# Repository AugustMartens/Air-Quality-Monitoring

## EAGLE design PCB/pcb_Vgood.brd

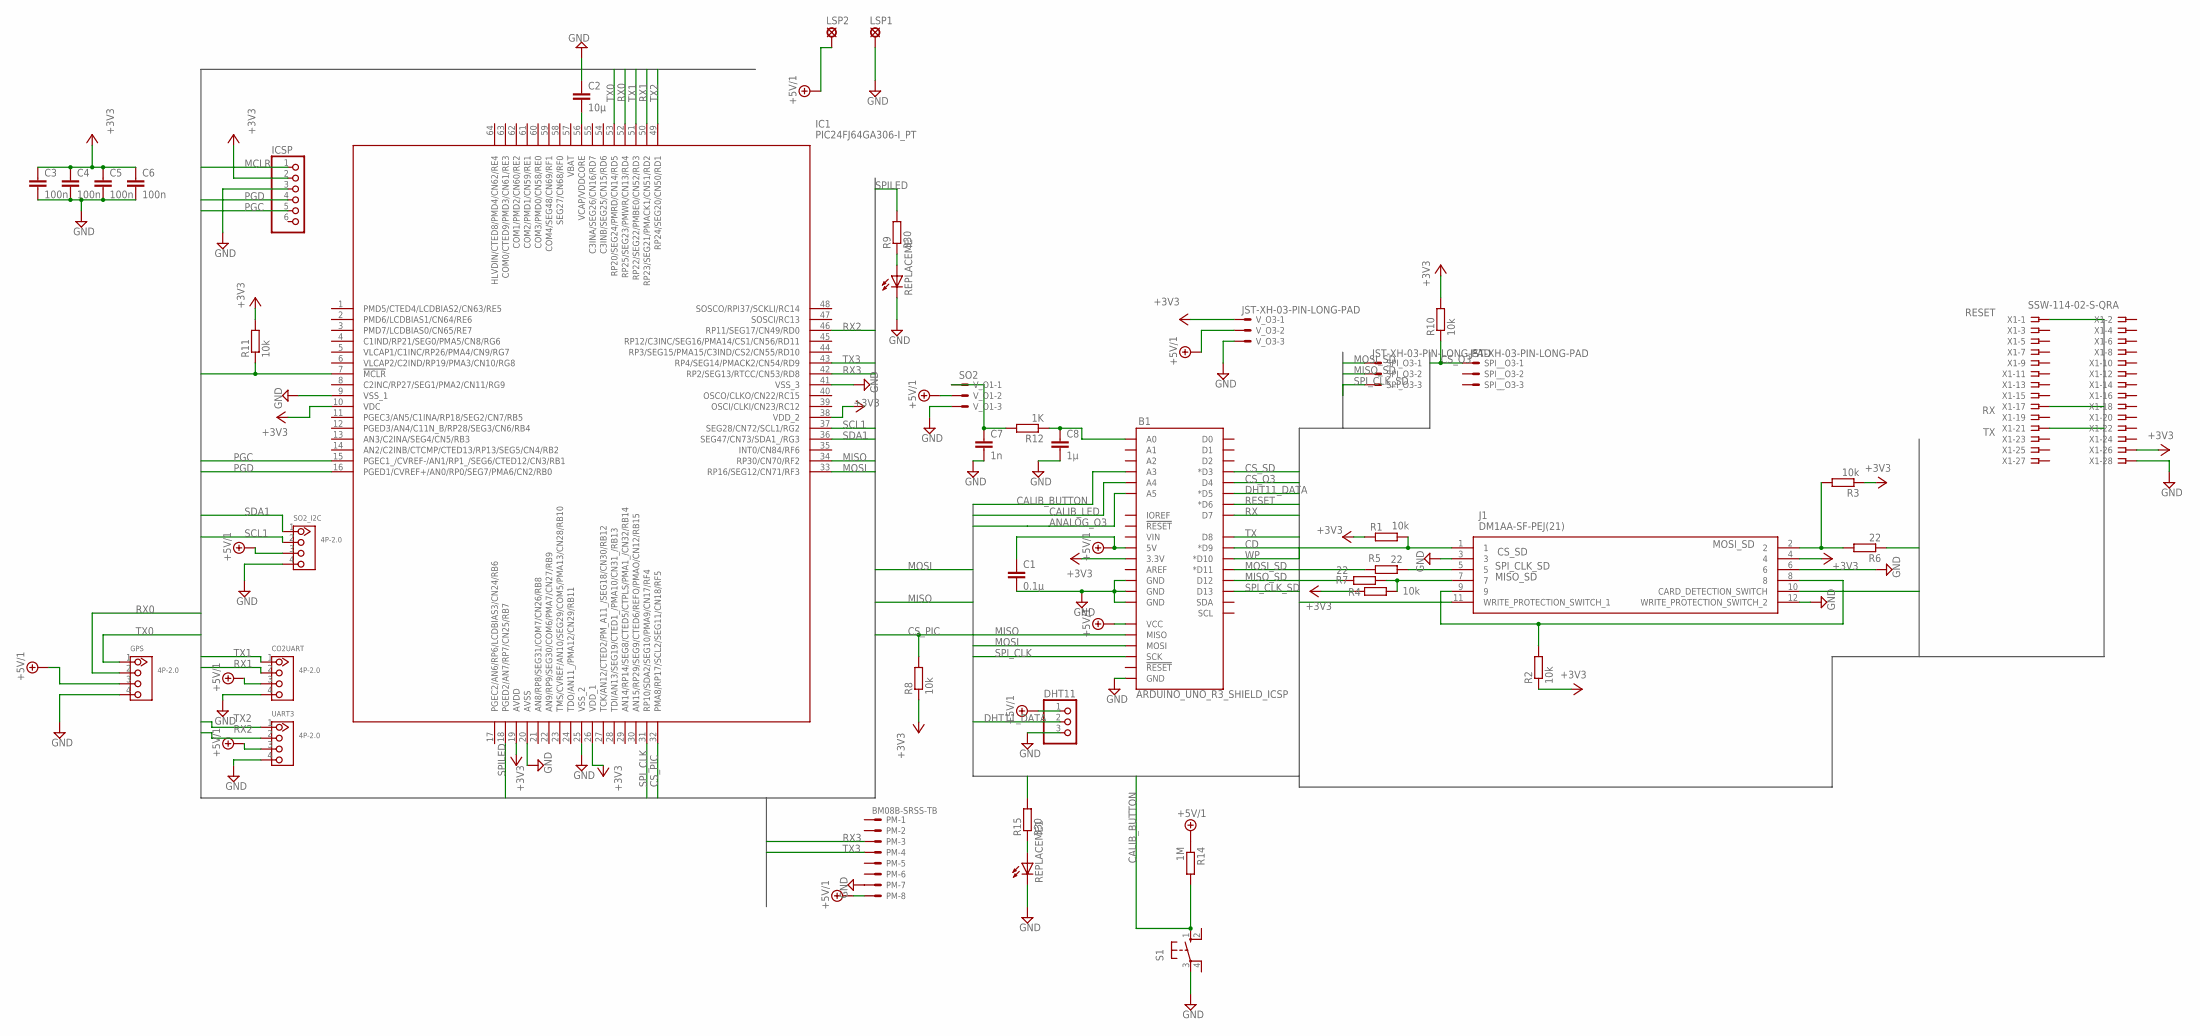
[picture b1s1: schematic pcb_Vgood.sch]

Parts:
B1: ARDUINO_UNO_R3_SHIELD_ICSP; UNO_R3_SHIELD_ICSP
C1: 0.1µ; C0805
C2: 10µ; C0805
C3, C4, C5, C6: 100n; C0805
C7: 1n; C0805
C8: 1µ; C0805
CO2UART: 4P-2.0; HW4-2.0
DHT11: PINHD-1X3; 1X03
GPS: 4P-2.0; HW4-2.0
IC1: PIC24FJ64GA306-I_PT; QFP50P1200X1200X120-64N
ICSP: PINHD-1X6; 1X06
J1: DM1AA-SF-PEJ(21); DM1AA-SF-PEJ(21)_1
LSP1: GND; SE14
LSP2: 5V; SE14
PM: BM08B-SRSS-TB
R1, R2, R3, R4, R8, R10, R11: 10k; M0805
R5, R6, R7: 22; M0805
R9, R15: 330; M0805
R12: 1K; M0805
R14: 1M; M0805
REPLACEME, REPLACEME1: LEDCHIP-LED0805; CHIP-LED0805
S1: 10-XX; B3F-10XX
SO2_I2C: 4P-2.0; HW4-2.0
SPI_O3: JST-XH-03-PIN-LONG-PAD; JST-XH-03-PACKAGE-LONG-PAD
SPI__O3: JST-XH-03-PIN-LONG-PAD; JST-XH-03-PACKAGE-LONG-PAD
UART3: 4P-2.0; HW4-2.0
V_O1: SO2; JST-XH-03-PACKAGE-LONG-PAD
V_O3: JST-XH-03-PIN-LONG-PAD; JST-XH-03-PACKAGE-LONG-PAD
X1: SSW-114-02-S-QRA; SSW-114-02-S-Q-RA

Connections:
+3V3: B1.3.3V, C3.1, C4.1, C5.1, C6.1, IC1.10 (VDC), IC1.19 (AVDD), IC1.26 (VDD_1), IC1.38 (VDD_2), ICSP.2, J1.4, R1.1, R2.1, R3.1, R4.1, R8.1, R10.2, R11.2, V_O3.1, X1.26
+5V/1: B1.5V, B1.5V_ICSP (VCC), C1.1, CO2UART.3, DHT11.1, GPS.3, LSP2.MP, PM.8, R14.1, SO2_I2C.3, UART3.3, V_O1.2, V_O3.2
ANALOG_O3: B1.A5
CALIB_BUTTON: B1.A3, R14.2, S1.1 (S)
CALIB_LED: B1.A4, R15.2
CD: B1.D9 (*D9), J1.10 (CARD_DETECTION_SWITCH)
CS_O3: B1.D4, R10.1, SPI__O3.1
CS_PIC: IC1.32 (PMA8/RP17/SCL2/SEG11/CN18/RF5), R8.2
CS_SD: B1.D3 (*D3), J1.1, R1.2
DHT11_DATA: B1.D5 (*D5), DHT11.2
GND: B1.GND@0 (GND), B1.GND@1 (GND), B1.GND@2 (GND), B1.GND_ICSP (GND), C1.2, C2.1, C3.2, C4.2, C5.2, C6.2, C7.2, C8.2, CO2UART.4, DHT11.3, GPS.4, IC1.9 (VSS_1), IC1.20 (AVSS), IC1.25 (VSS_2), IC1.41 (VSS_3), ICSP.3, J1.3, J1.6, J1.12 (WRITE_PROTECTION_SWITCH_2), LSP1.MP, PM.7, REPLACEME.C, REPLACEME1.C, S1.3, SO2_I2C.4, UART3.4, V_O1.3, V_O3.3, X1.28
MCLR: IC1.7 (!MCLR), ICSP.1, R11.1
MISO: B1.MISO, IC1.34 (RP30/CN70/RF2)
MISO_SD: B1.D12, R7.2, SPI_O3.2
MOSI: B1.MOSI, IC1.33 (RP16/SEG12/CN71/RF3)
MOSI_SD: B1.D11 (*D11), R6.1, SPI_O3.1
unnamed: R9.1, REPLACEME.A
unnamed: J1.8, J1.9, R2.2
unnamed: J1.5, R5.1
unnamed: C2.2, IC1.56 (VCAP/VDDCORE)
unnamed: R15.1, REPLACEME1.A
unnamed: J1.2, R3.2, R6.2
unnamed: J1.7, R4.2, R7.1
unnamed: B1.A0, C8.1, R12.1
unnamed: C7.1, R12.2, V_O1.1
PGC: IC1.15 (PGEC1_/CVREF-/AN1/RP1_/SEG6/CTED12/CN3/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), ICSP.5
PGD: IC1.16 (PGED1/CVREF+/AN0/RP0/SEG7/PMA6/CN2/RB0), ICSP.4
RESET: B1.D6 (*D6), X1.1
RX: B1.D7, X1.17
RX0: GPS.2, IC1.52 (RP25/SEG23/PMWR/CN13/RD4)
RX1: CO2UART.2, IC1.50 (RP23/SEG21/PMACK1/CN51/RD2)
RX2: IC1.46 (RP11/SEG17/CN49/RD0), UART3.2
RX3: IC1.42 (RP2/SEG13/RTCC/CN53/RD8), PM.3
SCL1: IC1.37 (SEG28/CN72/SCL1/RG2), SO2_I2C.2
SDA1: IC1.36 (SEG47/CN73/SDA1_/RG3), SO2_I2C.1
SPILED: IC1.18 (PGED2/AN7/RP7/CN25/RB7), R9.2
SPI_CLK: B1.SCK, IC1.31 (RP10/SDA2/SEG10/PMA9/CN17/RF4)
SPI_CLK_SD: B1.D13, R5.2, SPI_O3.3
TX: B1.D8, X1.21
TX0: GPS.1, IC1.53 (RP20/SEG24/PMRD/CN14/RD5)
TX1: CO2UART.1, IC1.51 (RP22/SEG22/PMBE0/CN52/RD3)
TX2: IC1.49 (RP24/SEG20/CN50/RD1), UART3.1
TX3: IC1.43 (RP4/SEG14/PMACK2/CN54/RD9), PM.4
WP: B1.D10 (*D10), J1.11 (WRITE_PROTECTION_SWITCH_1)

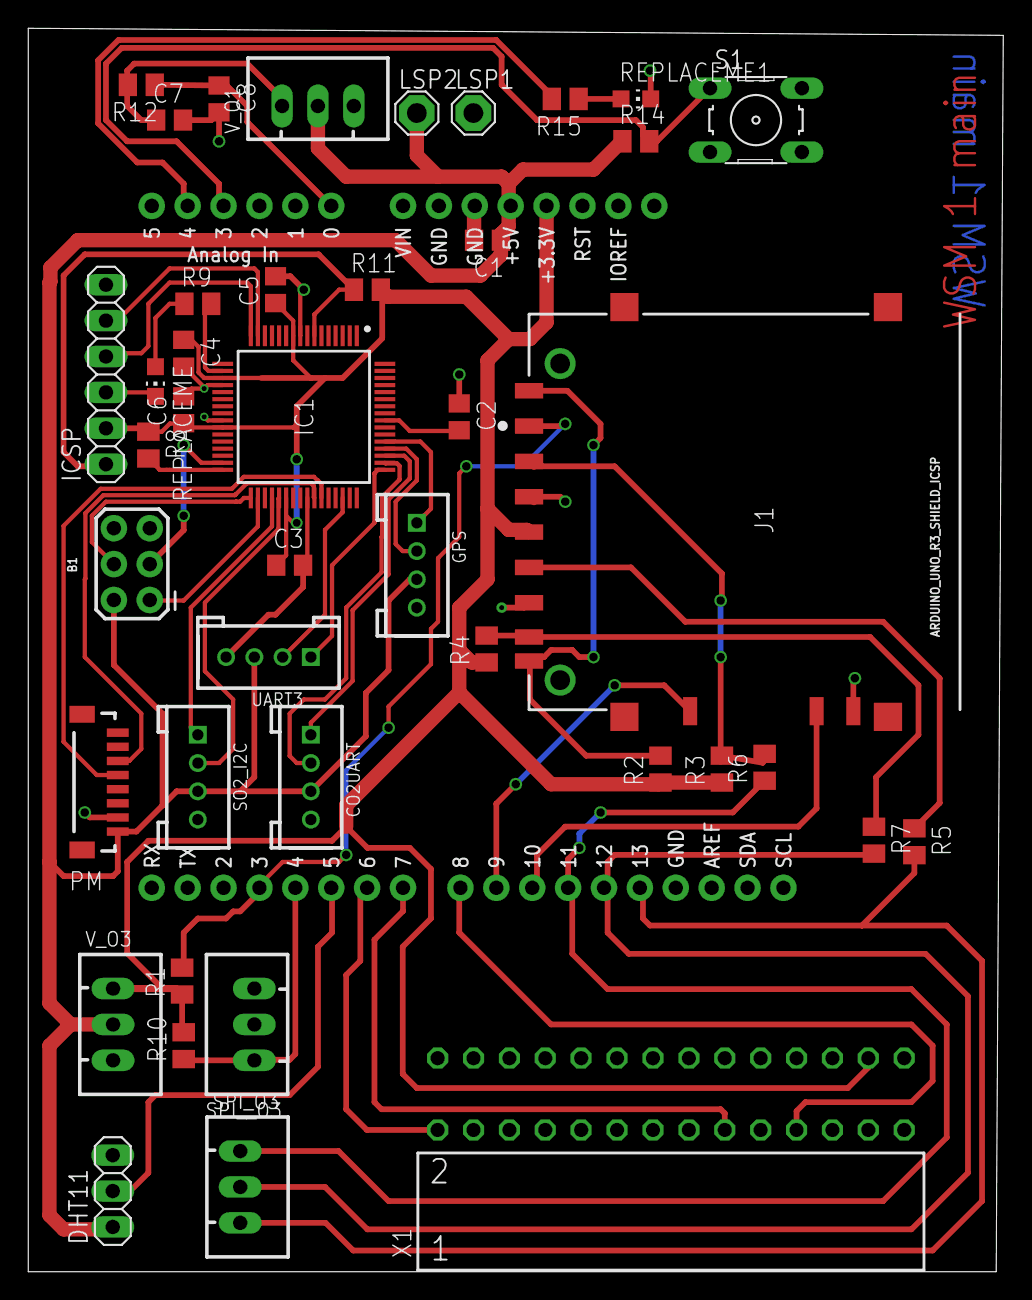
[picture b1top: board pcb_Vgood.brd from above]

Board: 2 copper layers, 69.0 x 88.0 mm, 42 parts (0 on the bottom side), 43 nets.

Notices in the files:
parts and their libraries:
SparkFun-Boards: Licensing: Creative Commons ShareAlike 4.0 International - https://creativecommons.org/licenses/by-sa/4.0
